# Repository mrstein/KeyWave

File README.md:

# KeyWave
Arduino based car sharing solution

Work In Progress:
- android APK need some improvement. 
- New hardware version with SIM900, NFC reader and linear motor

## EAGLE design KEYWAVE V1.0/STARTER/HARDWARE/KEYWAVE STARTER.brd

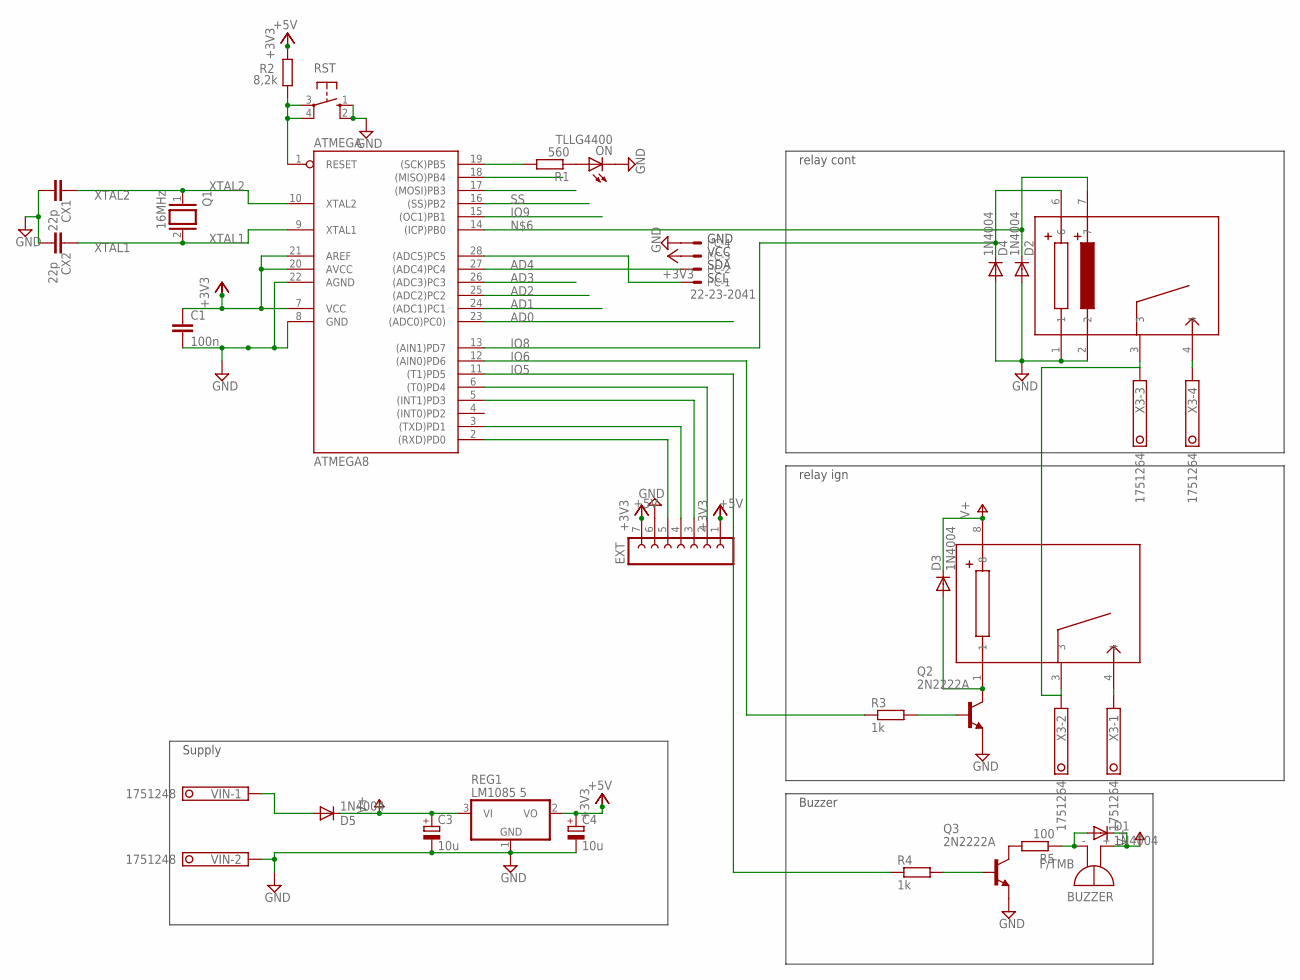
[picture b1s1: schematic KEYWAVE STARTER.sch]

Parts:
ATMEGA: ATMEGA8; DIL28-3
BUZZER: F/TMB
C1: 100n; C050-030X075
C3, C4: 10u; E5-6
CONTACT: D6BK-1114P; D6BK-1114C
CX1, CX2: 22p; C0603-ROUND
D1, D2, D3, D4, D5: 1N4004; DO41-10
EXT: FE07-1; FE07
I²C: 22-23-2041
ON: TLLG4400; LED3MM
Q1: 16MHz; QS
Q2, Q3: 2N2222A; TO18
R1: 560; 0207/10
R2: 8,2k; 0207/10
R3, R4: 1k; 0207/10
R5: 100; 0207/10
REG1: LM1085 5; TO220
RST: 10-XX; B3F-10XX
STARTER: DK1-L1-12V
VIN: 1751248
X3: 1751264

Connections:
+3V3: ATMEGA.7 (VCC), ATMEGA.20 (AVCC), ATMEGA.21 (AREF), C1.1, C4.+, EXT.1, EXT.7, I²C.3, R2.2, REG1.2 (VO)
AD0: ATMEGA.23 ((ADC0)PC0))
AD1: ATMEGA.24 ((ADC1)PC1)
AD2: ATMEGA.25 ((ADC2)PC2)
AD3: ATMEGA.26 ((ADC3)PC3)
AD4: ATMEGA.27 ((ADC4)PC4), I²C.2
GND: ATMEGA.8 (GND), ATMEGA.22 (AGND), C1.2, C3.-, C4.-, CONTACT.1, CONTACT.2, CX1.1, CX2.1, D2.A, D4.A, EXT.6, I²C.4, ON.K (C), Q2.1 (E), Q3.1 (E), REG1.1 (GND), RST.1 (S), RST.2 (S1), VIN.2
IO5: ATMEGA.11 ((T1)PD5), R4.1
IO6: ATMEGA.12 ((AIN0)PD6), R3.1
IO8: ATMEGA.13 ((AIN1)PD7), CONTACT.6, D4.C
IO9: ATMEGA.15 ((OC1)PB1)
MISO: ATMEGA.18 ((MISO)PB4)
MOSI: ATMEGA.17 ((MOSI)PB3)
unnamed: STARTER.4, X3.1
unnamed: Q3.3 (C), R5.2
unnamed: D5.A, VIN.1
unnamed: Q2.2 (B), R3.2
unnamed: ATMEGA.14 ((ICP)PB0), CONTACT.7, D2.C
unnamed: CONTACT.3, STARTER.3, X3.2, X3.3
unnamed: ATMEGA.28 ((ADC5)PC5), I²C.1
unnamed: CONTACT.4, X3.4
unnamed: ATMEGA.2 ((RXD)PD0), EXT.5
unnamed: ATMEGA.3 ((TXD)PD1), EXT.4
unnamed: ATMEGA.5 ((INT1)PD3), EXT.3
unnamed: ATMEGA.6 ((T0)PD4), EXT.2
unnamed: Q3.2 (B), R4.2
unnamed: D3.A, Q2.3 (C), STARTER.1
unnamed: BUZZER.-, D1.A, R5.1
unnamed: ON.A, R1.1
RESET: ATMEGA.1 (RESET), R2.1, RST.3, RST.4 (P1)
SCK: ATMEGA.19 ((SCK)PB5), R1.2
SS: ATMEGA.16 ((SS)PB2)
V+: BUZZER.+, C3.+, D1.C, D3.C, D5.C, REG1.3 (VI), STARTER.8
XTAL1: ATMEGA.9 (XTAL1), CX2.2, Q1.2
XTAL2: ATMEGA.10 (XTAL2), CX1.2, Q1.1

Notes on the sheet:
Supply
Buzzer
relay ign
relay cont
SDA
SCL
GND
VCC

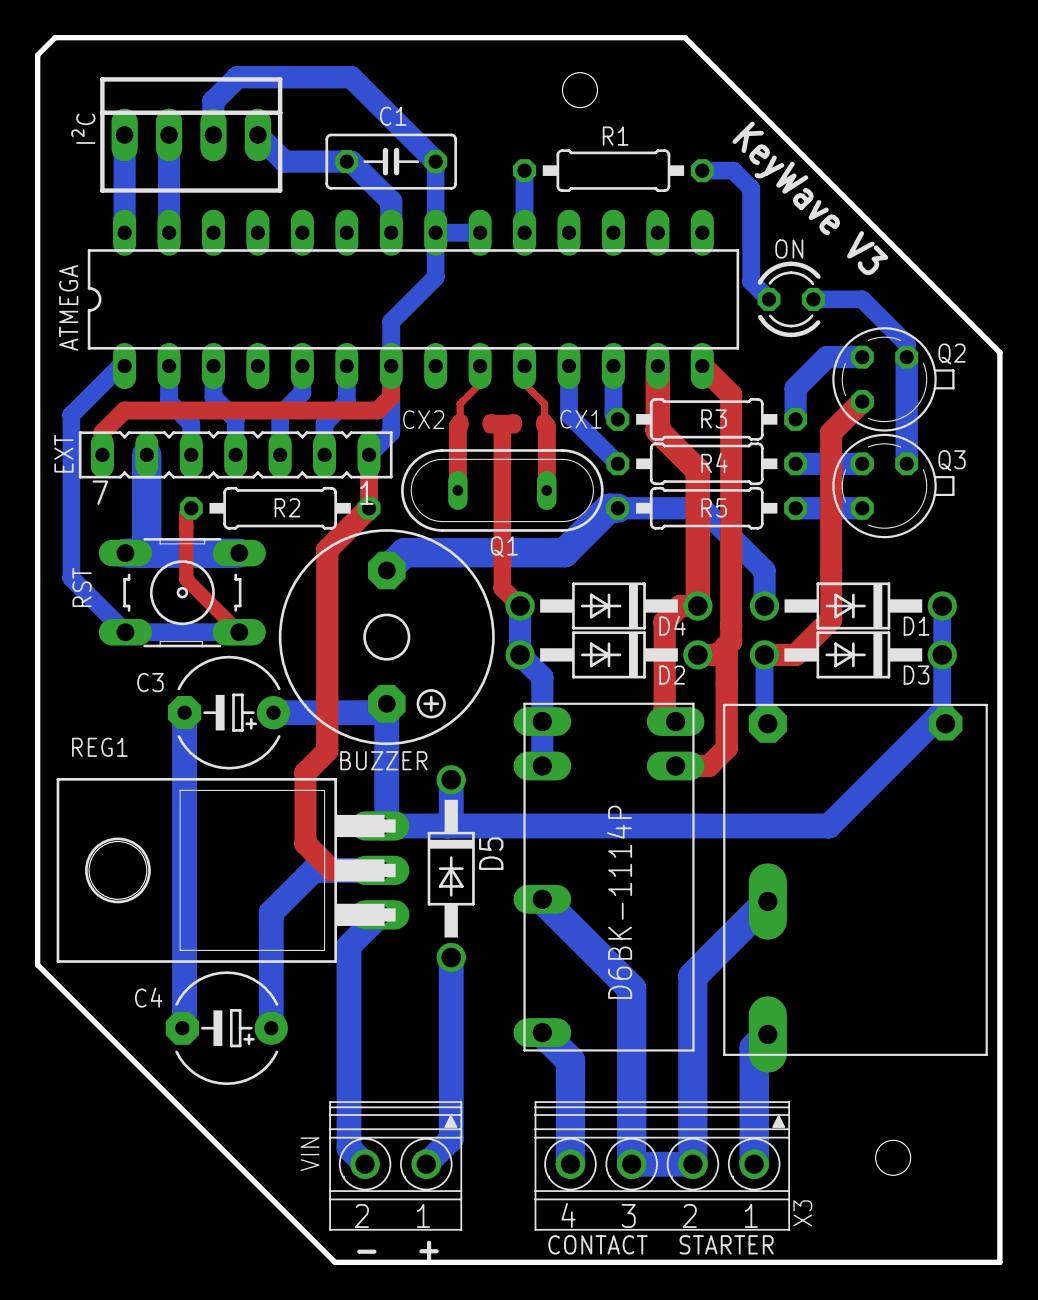
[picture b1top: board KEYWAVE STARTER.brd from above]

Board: 2 copper layers, 55.0 x 70.0 mm, 29 parts (0 on the bottom side), 27 nets.

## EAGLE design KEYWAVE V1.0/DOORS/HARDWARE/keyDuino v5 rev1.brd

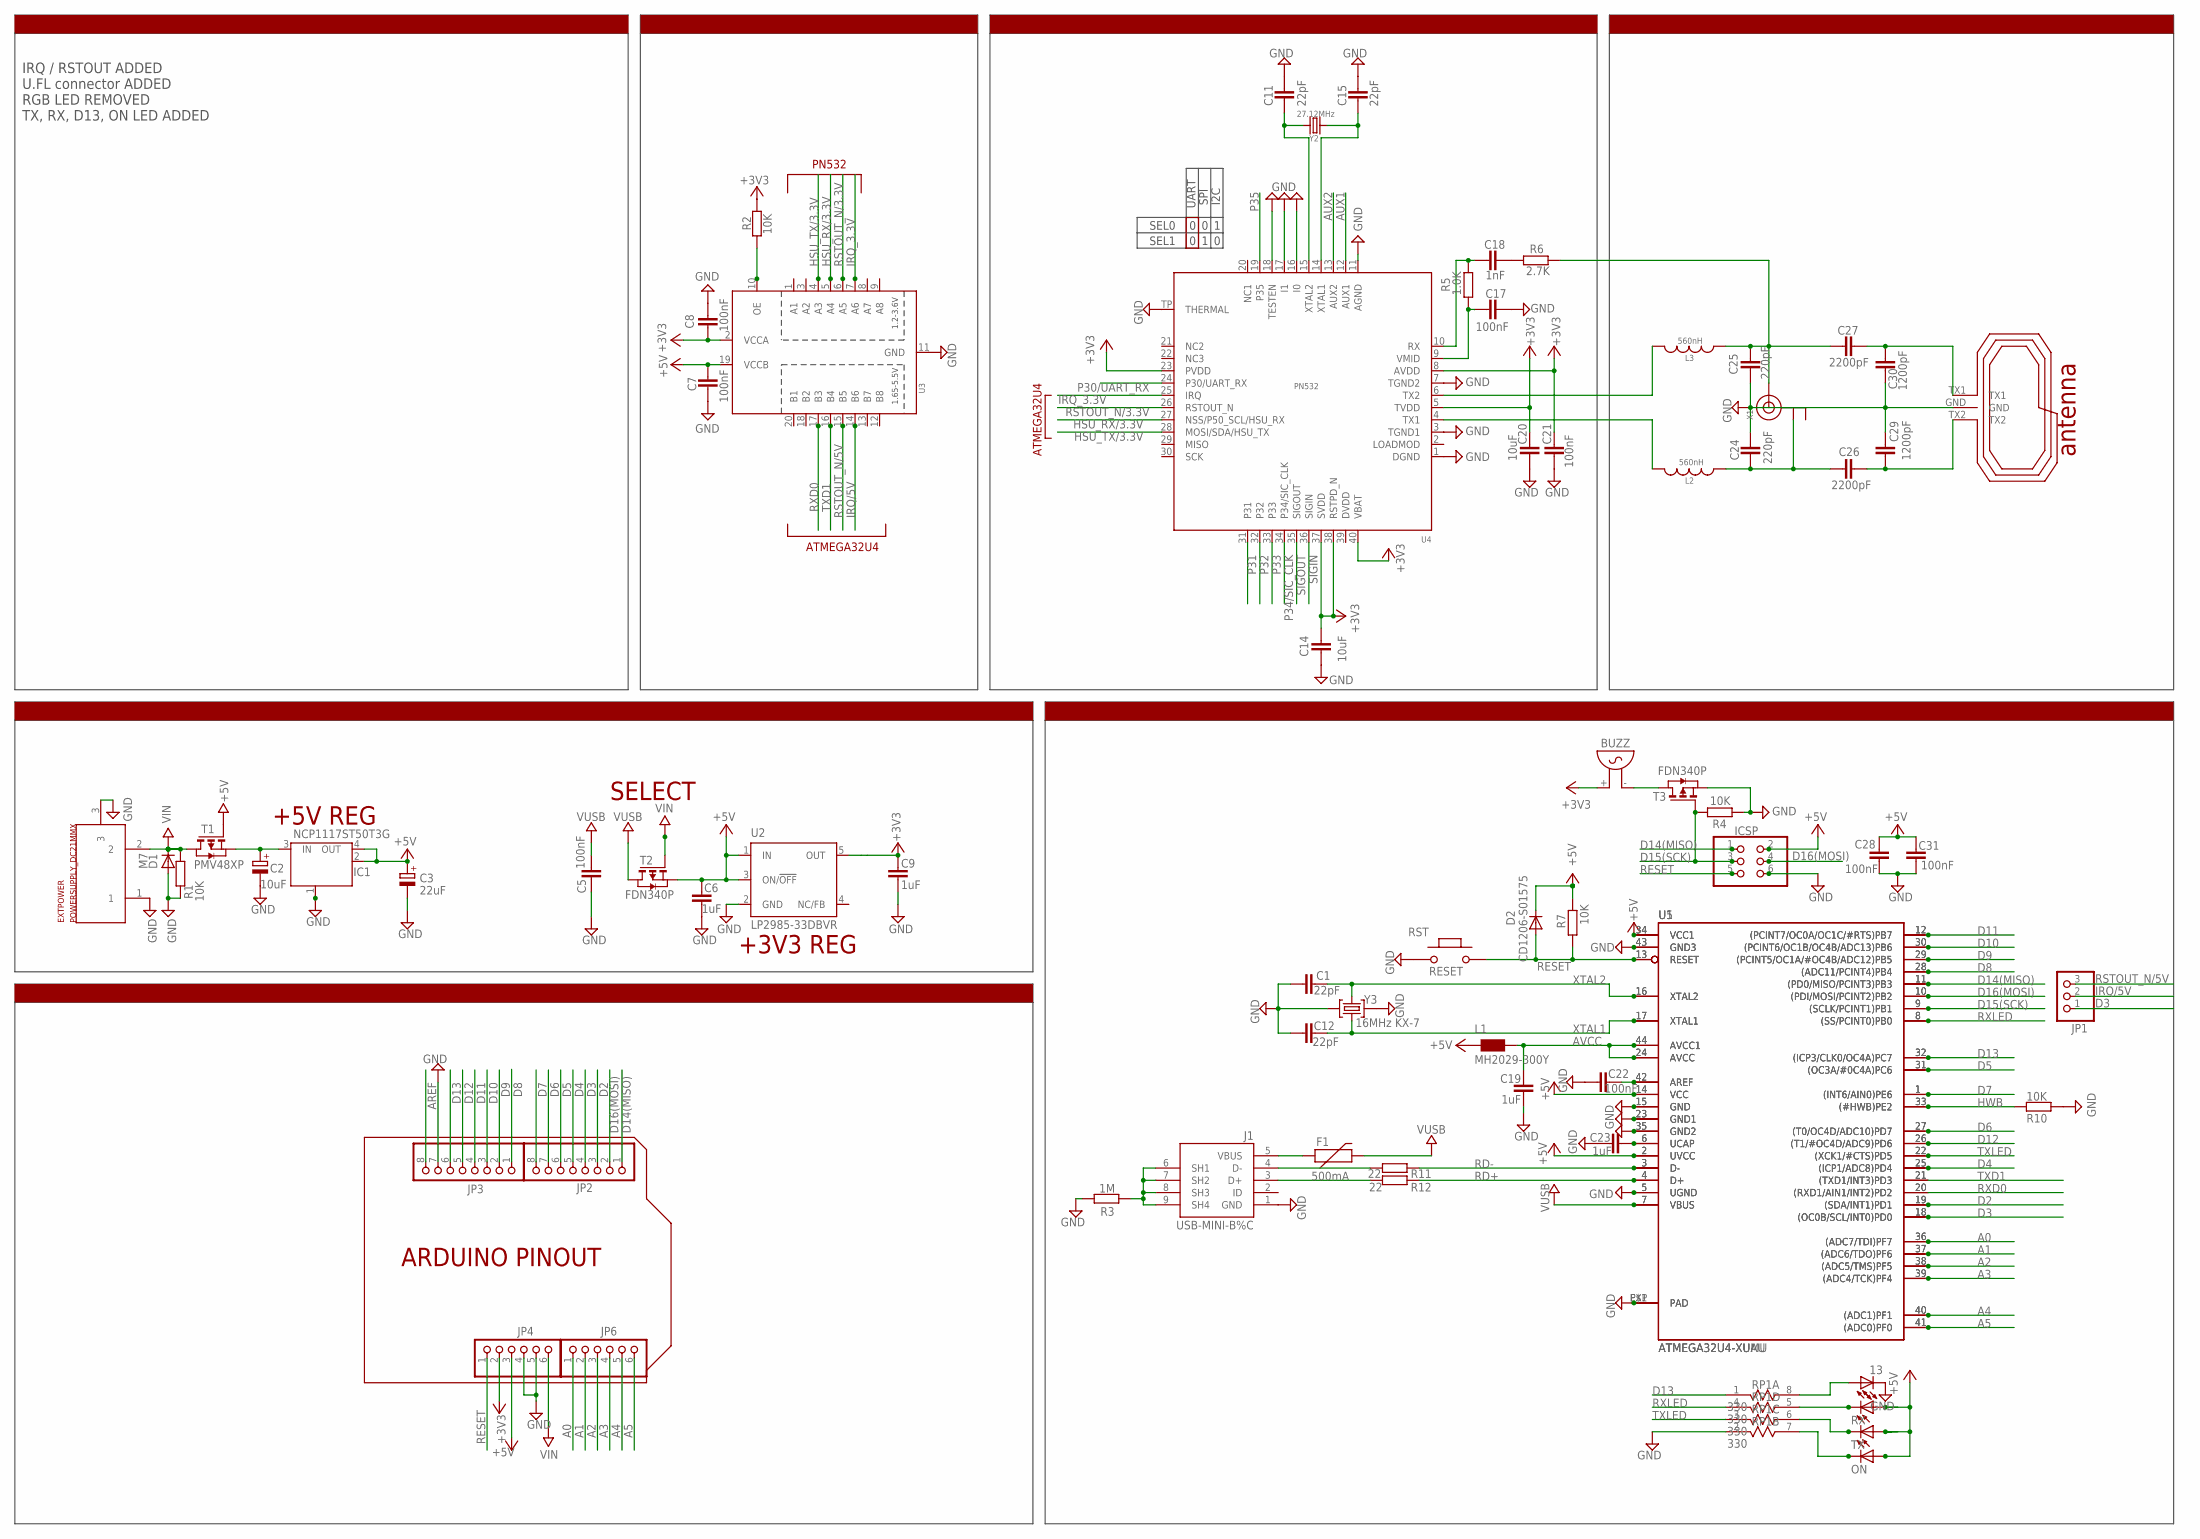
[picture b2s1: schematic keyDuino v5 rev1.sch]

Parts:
13: LEDCHIPLED_0603; CHIPLED_0603
BUZZ: F/QMX
C1, C11, C12, C15: 22pF; 0603-CAP
C2: 10uF; SMC_B
C3: 22uF; SMC_B
C5, C7, C8, C17, C22, C28, C31: 100nF; C0603
C6, C9, C19, C23: 1uF; C0603
C14, C20: 10uF; C0805
C18: 1nF; C0603
C21: 100nF; C0805
C24, C25: 220pF; C0603
C26, C27: 2200pF; C0603
C29, C30: 1200pF; C0603
D1: M7; SMB
D2: CD1206-S01575; MINIMELF
EXTPOWER: POWERSUPPLY_DC21MMX; POWERSUPPLY_DC-21MM
F1: 500mA; PTC-1206
IC1: NCP1117ST50T3G; SOT223
ICSP: ICSP; 2X03
J1: USB-MINI-B%C; USB-MINI-B_2
JP1: PINHD-1X3; 1X03
JP2, JP3: PINHD-1X8CLEANBIG; 1X08-CLEANBIG
JP4, JP6: PINHD-1X6CB; 1X06-CLEANBIG
L1: MH2029-300Y; 0805
L2, L3: 560nH; 0805@1
ON: LEDCHIPLED_0603; CHIPLED_0603
R1, R2, R4, R7, R10: 10K; R0603
R3: 1M; R0805
R5: 1.0K; R0603
R6: 2.7K; R0603
R11, R12: 22; R0603
RP1: 330; RES4NT
RST: RESET; 157SW
RX: LEDCHIPLED_0603; CHIPLED_0603
T1: PMV48XP; SOT-23
T2, T3: FDN340P; SOT-23
TX: LEDCHIPLED_0603; CHIPLED_0603
U1: ATMEGA32U4-XUAU; TQFP44-PAD
U2: LP2985-33DBVR; SOT23-DBV
U3: TXB0108PWR; TSSOP20
U4: PN532; HVQFN40-6X6
U5: ATMEGA32U4-XUMU; QFN44ML7X7
U$1: ANT_V3; ANT_13.56_P4
X1: ANTENNA_U.FL; U.FL
Y2: 27.12MHz; CRYSTAL_3.2X2.5
Y3: 16MHz KX-7; CRYSTAL-3.2-2.5

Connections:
+3V3: BUZZ.+ (2), C8.1, C9.2, C14.2, C20.2, C21.2, JP4.2, R2.1, U2.5 (OUT), U3.2 (VCCA), U4.5 (TVDD), U4.8 (AVDD), U4.23 (PVDD), U4.37 (SVDD), U4.38 (RSTPD_N), U4.40 (VBAT)
+5V: C3.+, C6.2, C7.2, C28.1, C31.1, D2.C, IC1.2 (OUT), IC1.4 (OUT), ICSP.2, JP4.3, L1.1, ON.A, R7.1, RX.A, T1.3 (G), T2.2 (S), TX.A, U1.2 (UVCC), U1.14 (VCC), U1.34 (VCC1), U2.1 (IN), U2.3 (ON/!OFF), U3.19 (VCCB), U5.2 (UVCC), U5.14 (VCC), U5.34 (VCC1)
A0: JP6.1, U1.36 ((ADC7/TDI)PF7), U5.36 ((ADC7/TDI)PF7)
A1: JP6.2, U1.37 ((ADC6/TDO)PF6), U5.37 ((ADC6/TDO)PF6)
A2: JP6.3, U1.38 ((ADC5/TMS)PF5), U5.38 ((ADC5/TMS)PF5)
A3: JP6.4, U1.39 ((ADC4/TCK)PF4), U5.39 ((ADC4/TCK)PF4)
A4: JP6.5, U1.40 ((ADC1)PF1), U5.40 ((ADC1)PF1)
A5: JP6.6, U1.41 ((ADC0)PF0), U5.41 ((ADC0)PF0)
AREF: C22.1, JP3.8, U1.42 (AREF), U5.42 (AREF)
AUX1: U4.12 (AUX1)
AUX2: U4.13 (AUX2)
AVCC: C19.1, L1.2, U1.24 (AVCC), U1.44 (AVCC1), U5.24 (AVCC), U5.44 (AVCC1)
B1: 13.A, RP1.8 (2)
CON1: C24.2, C26.1, L2.1, X1.1 (GND)
D2: JP2.3, U1.19 ((SDA/INT1)PD1), U5.19 ((SDA/INT1)PD1)
D3: JP1.1, JP2.4, U1.18 ((OC0B/SCL/INT0)PD0), U5.18 ((OC0B/SCL/INT0)PD0)
D4: JP2.5, U1.25 ((ICP1/ADC8)PD4), U5.25 ((ICP1/ADC8)PD4)
D5: JP2.6, U1.31 ((OC3A/#0C4A)PC6), U5.31 ((OC3A/#0C4A)PC6)
D6: JP2.7, U1.27 ((T0/OC4D/ADC10)PD7), U5.27 ((T0/OC4D/ADC10)PD7)
D7: JP2.8, U1.1 ((INT6/AIN0)PE6), U5.1 ((INT6/AIN0)PE6)
D8: JP3.1, U1.28 ((ADC11/PCINT4)PB4), U5.28 ((ADC11/PCINT4)PB4)
D9: JP3.2, U1.29 ((PCINT5/OC1A/#OC4B/ADC12)PB5), U5.29 ((PCINT5/OC1A/#OC4B/ADC12)PB5)
D10: JP3.3, U1.30 ((PCINT6/OC1B/OC4B/ADC13)PB6), U5.30 ((PCINT6/OC1B/OC4B/ADC13)PB6)
D11: JP3.4, U1.12 ((PCINT7/OC0A/OC1C/#RTS)PB7), U5.12 ((PCINT7/OC0A/OC1C/#RTS)PB7)
D12: JP3.5, U1.26 ((T1/#OC4D/ADC9)PD6), U5.26 ((T1/#OC4D/ADC9)PD6)
D13: JP3.6, RP1.1, U1.32 ((ICP3/CLK0/OC4A)PC7), U5.32 ((ICP3/CLK0/OC4A)PC7)
D14(MISO): ICSP.1, JP2.1, U1.11 ((PD0/MISO/PCINT3)PB3), U5.11 ((PD0/MISO/PCINT3)PB3)
D15(SCK): ICSP.3, R4.1, T3.3 (G), U1.9 ((SCLK/PCINT1)PB1), U5.9 ((SCLK/PCINT1)PB1)
D16(MOSI): ICSP.4, JP2.2, U1.10 ((PDI/MOSI/PCINT2)PB2), U5.10 ((PDI/MOSI/PCINT2)PB2)
G1: RP1.5 (2), RX.C
GND: 13.C, C1.1, C2.-, C3.-, C5.1, C6.1, C7.1, C8.2, C9.1, C11.1, C12.1, C14.1, C15.1, C17.1, C19.2, C20.1, C21.1, C22.2, C23.2, C24.1, C25.2, C28.2, C29.1, C30.2, C31.2, D1.A, EXTPOWER.1, EXTPOWER.3, IC1.1 (GND/ADJ), ICSP.6, J1.1 (GND), JP3.7, JP4.4, JP4.5, R1.1, R3.1, R4.2, R10.2, RP1.2 (1), RST.1, T3.2 (S), U1.5 (UGND), U1.15 (GND), U1.23 (GND1), U1.35 (GND2), U1.43 (GND3), U1.P$1 (PAD), U2.2 (GND), U3.11 (GND), U4.1 (DGND), U4.3 (TGND1), U4.7 (TGND2), U4.11 (AGND), U4.16 (I0), U4.17 (I1), U4.18 (TESTEN), U4.TP (THERMAL), U5.5 (UGND), U5.15 (GND), U5.23 (GND1), U5.35 (GND2), U5.43 (GND3), U5.EXP (PAD), U$1.GND, Y3.2 (GND), Y3.4 (GND)
HSU_RX/3.3V: U3.5 (A4), U4.27 (NSS/P50_SCL/HSU_RX)
HSU_TX/3.3V: U3.4 (A3), U4.28 (MOSI/SDA/HSU_TX)
HWB: R10.1, U1.33 ((#HWB)PE2), U5.33 ((#HWB)PE2)
IRQ/5V: JP1.2, U3.14 (B6)
IRQ_3.3V: U3.7 (A6), U4.25 (IRQ)
unnamed: BUZZ.- (1), T3.1 (D)
unnamed: F1.1, J1.5 (VBUS)
unnamed: J1.6 (SH1), J1.7 (SH2), J1.8 (SH3), J1.9 (SH4), R3.2
unnamed: C18.1, R6.1
unnamed: L2.2, U4.4 (TX1)
unnamed: L3.2, U4.6 (TX2)
unnamed: ON.C, RP1.7 (2)
unnamed: J1.4 (D-), R11.1
unnamed: J1.3 (D+), R12.1
unnamed: C2.+, IC1.3 (IN), T1.2 (S)
unnamed: R2.2, U3.10 (OE)
unnamed: C15.2, U4.14 (XTAL1), Y2.1
unnamed: C11.2, U4.15 (XTAL2), Y2.2
unnamed: C17.2, R5.2, U4.9 (VMID)
unnamed: C18.2, R5.1, U4.10 (RX)
P30/UART_RX: U4.24 (P30/UART_RX)
P31: U4.31
P32: U4.32
P33: U4.33
P34/SIC_CLK: U4.34 (P34/SIC_CLK)
P35: U4.19 (P35)
R1: RP1.6 (2), TX.C
RD+: R12.2, U1.4 (D+), U5.4 (D+)
RD-: R11.2, U1.3 (D-), U5.3 (D-)
RESET: D2.A, ICSP.5, JP4.1, R7.2, RST.2, U1.13 (RESET), U5.13 (RESET)
RSTOUT_N/3.3V: U3.6 (A5), U4.26 (RSTOUT_N)
RSTOUT_N/5V: JP1.3, U3.15 (B5)
RXD0: U1.20 ((RXD1/AIN1/INT2)PD2), U3.17 (B3), U5.20 ((RXD1/AIN1/INT2)PD2)
RXLED: RP1.4 (1), U1.8 ((SS/PCINT0)PB0), U5.8 ((SS/PCINT0)PB0)
SIGIN: U4.36 (SIGIN)
SIGOUT: U4.35 (SIGOUT)
TX1_ANTENNA: C26.2, C29.2, U$1.TX2
TX2_ANTENNA: C27.1, C30.1, U$1.TX1
TXD1: U1.21 ((TXD1/INT3)PD3), U3.16 (B4), U5.21 ((TXD1/INT3)PD3)
TXLED: RP1.3 (1), U1.22 ((XCK1/#CTS)PD5), U5.22 ((XCK1/#CTS)PD5)
UCAP: C23.1, U1.6 (UCAP), U5.6 (UCAP)
VIN: D1.C, EXTPOWER.2, JP4.6, R1.2, T1.1 (D), T2.3 (G)
VUSB: C5.2, F1.2, T2.1 (D), U1.7 (VBUS), U5.7 (VBUS)
XTAL1: C12.2, U1.17 (XTAL1), U5.17 (XTAL1), Y3.1 (C1)
XTAL2: C1.2, U1.16 (XTAL2), U5.16 (XTAL2), Y3.3 (C2)
XX1: C25.1, C27.2, L3.1, R6.2, X1.3 (SIGNAL)

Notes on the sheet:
ATMEGA32U4
+3V3 REG
SEL0
SEL1
UART
SPI
I2C
SELECT
SUPPLYs
+5V REG
convertisseur de niveau
PN532
ACCORDING CIRCUIT
PINOUT
ARDUINO PINOUT
MOD
IRQ / RSTOUT ADDED U.FL connector ADDED RGB LED REMOVED TX, RX, D13, ON LED ADDED

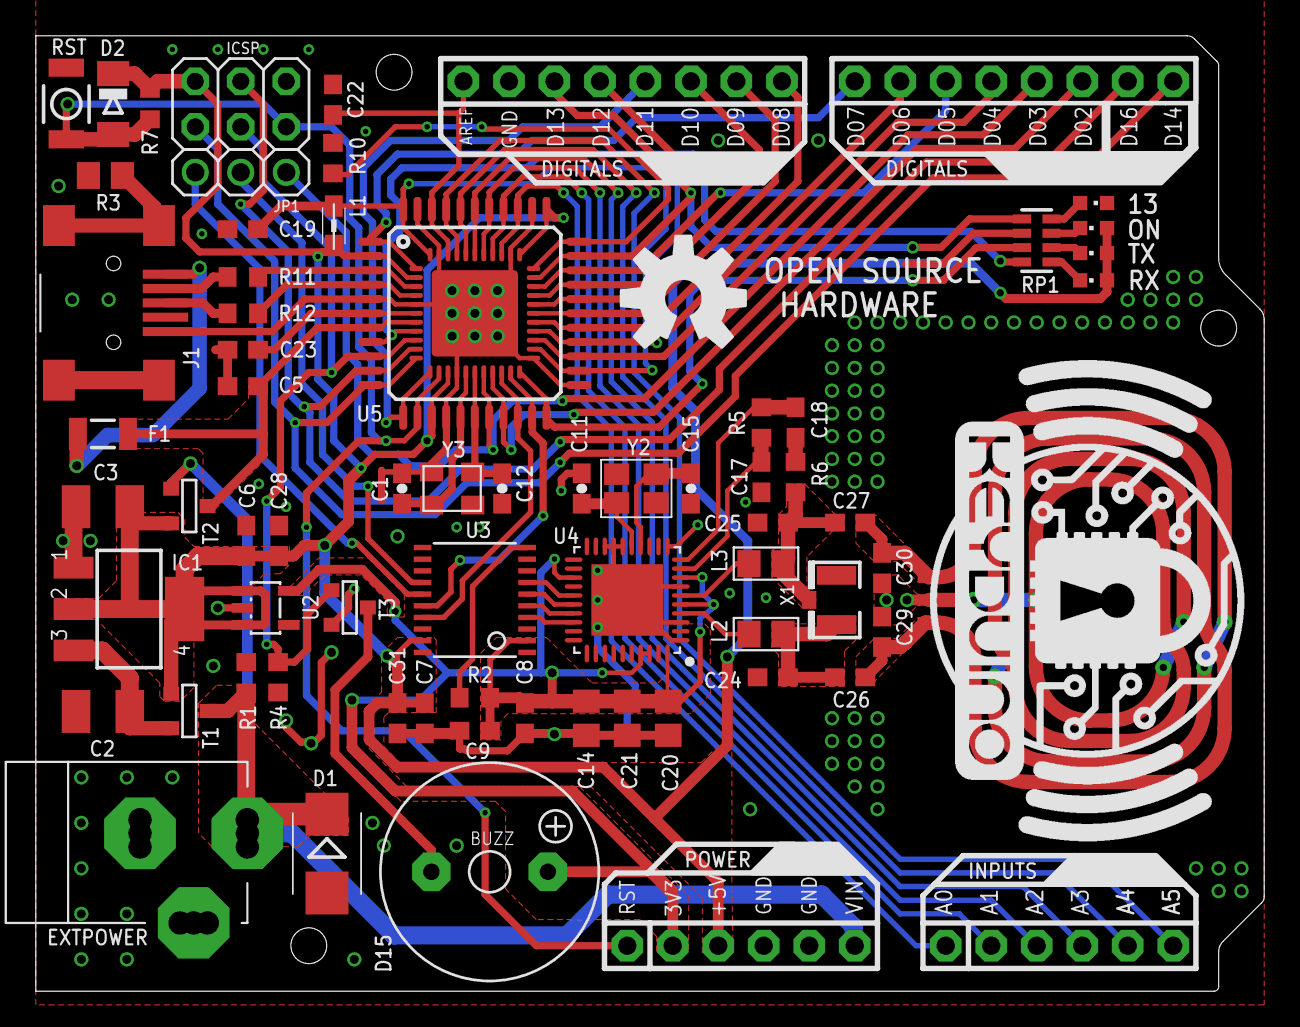
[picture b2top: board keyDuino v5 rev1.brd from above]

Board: 2 copper layers, 68.6 x 53.3 mm, 72 parts (0 on the bottom side), 67 nets.

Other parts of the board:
U$2: OSHW-LOGO-L

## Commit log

2017-12-03 Create READ ME

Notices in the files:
parts and their libraries:
SparkFun-Aesthetics: Licensing: Creative Commons ShareAlike 4.0 International - https://creativecommons.org/licenses/by-sa/4.0
